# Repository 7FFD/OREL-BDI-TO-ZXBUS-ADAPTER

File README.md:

# OREL-BDI-TO-ZXBUS-ADAPTER

The motivation to create such kind of adapter was a problem to find ready-to-solder boards for ZX Spectrum BDI.
Most of them were designed for specific clones and on Ukrainian marketplaces easily accessible was only boards for Orel BK.

A bit of history...

Somewhere in 2021 I soldered Harlequin 128k and as far as I played with Tape input, decided to expand and connect disk drive.
As I mentioned before, I faced mostly with BDI for Orel computer. Research had shown that all signals on the board were available on Harlequin ZXBUS Edge slot. So, I decided to give a chance and buy this adapter from one of sellers who stated that controller was tested and worked fine. Indeed, he sold DIY package with all components, so, itt was a huge plus.
After I received and soldered it, another kind of issue appeared - how to connect to Harlequin. Solder by wires ZXBUS Slot? Or something else?
I decided to go with adapter, on prototype board solder socket to connect controller and solder ZXBUS Slot with appropriate wiring.
This idea looked more reliable then just wires.

and...

Later I expanded this adapter with optional Kempston Joystick interface, separate TRDOS rom that can in different modes and simple protection schematics for IC KP1818VG93.

The latest version looked like Frankenstien...

Over a time I collected on prototype board quite a lot of useful features and implemented them on final schematic:
 -  Optional Kempston Joystic, can be off, always on or depends on BETA signal from Orel BDI
 -  Optional ROM, can be off, only TRDOS part activated and stock ROM with Basic, TRDOS and Basic in optional ROM, in addition, 27C512 can be used without schematic changes
 -  Magic Button
 -  External +12v
 -  Safe +12V for 1818VG93
 -  Block external Kempston Joystic by /KJOY connected to A28 on ZXBUS Slot

So, I decided make it more beatuful. This is how it looks now!

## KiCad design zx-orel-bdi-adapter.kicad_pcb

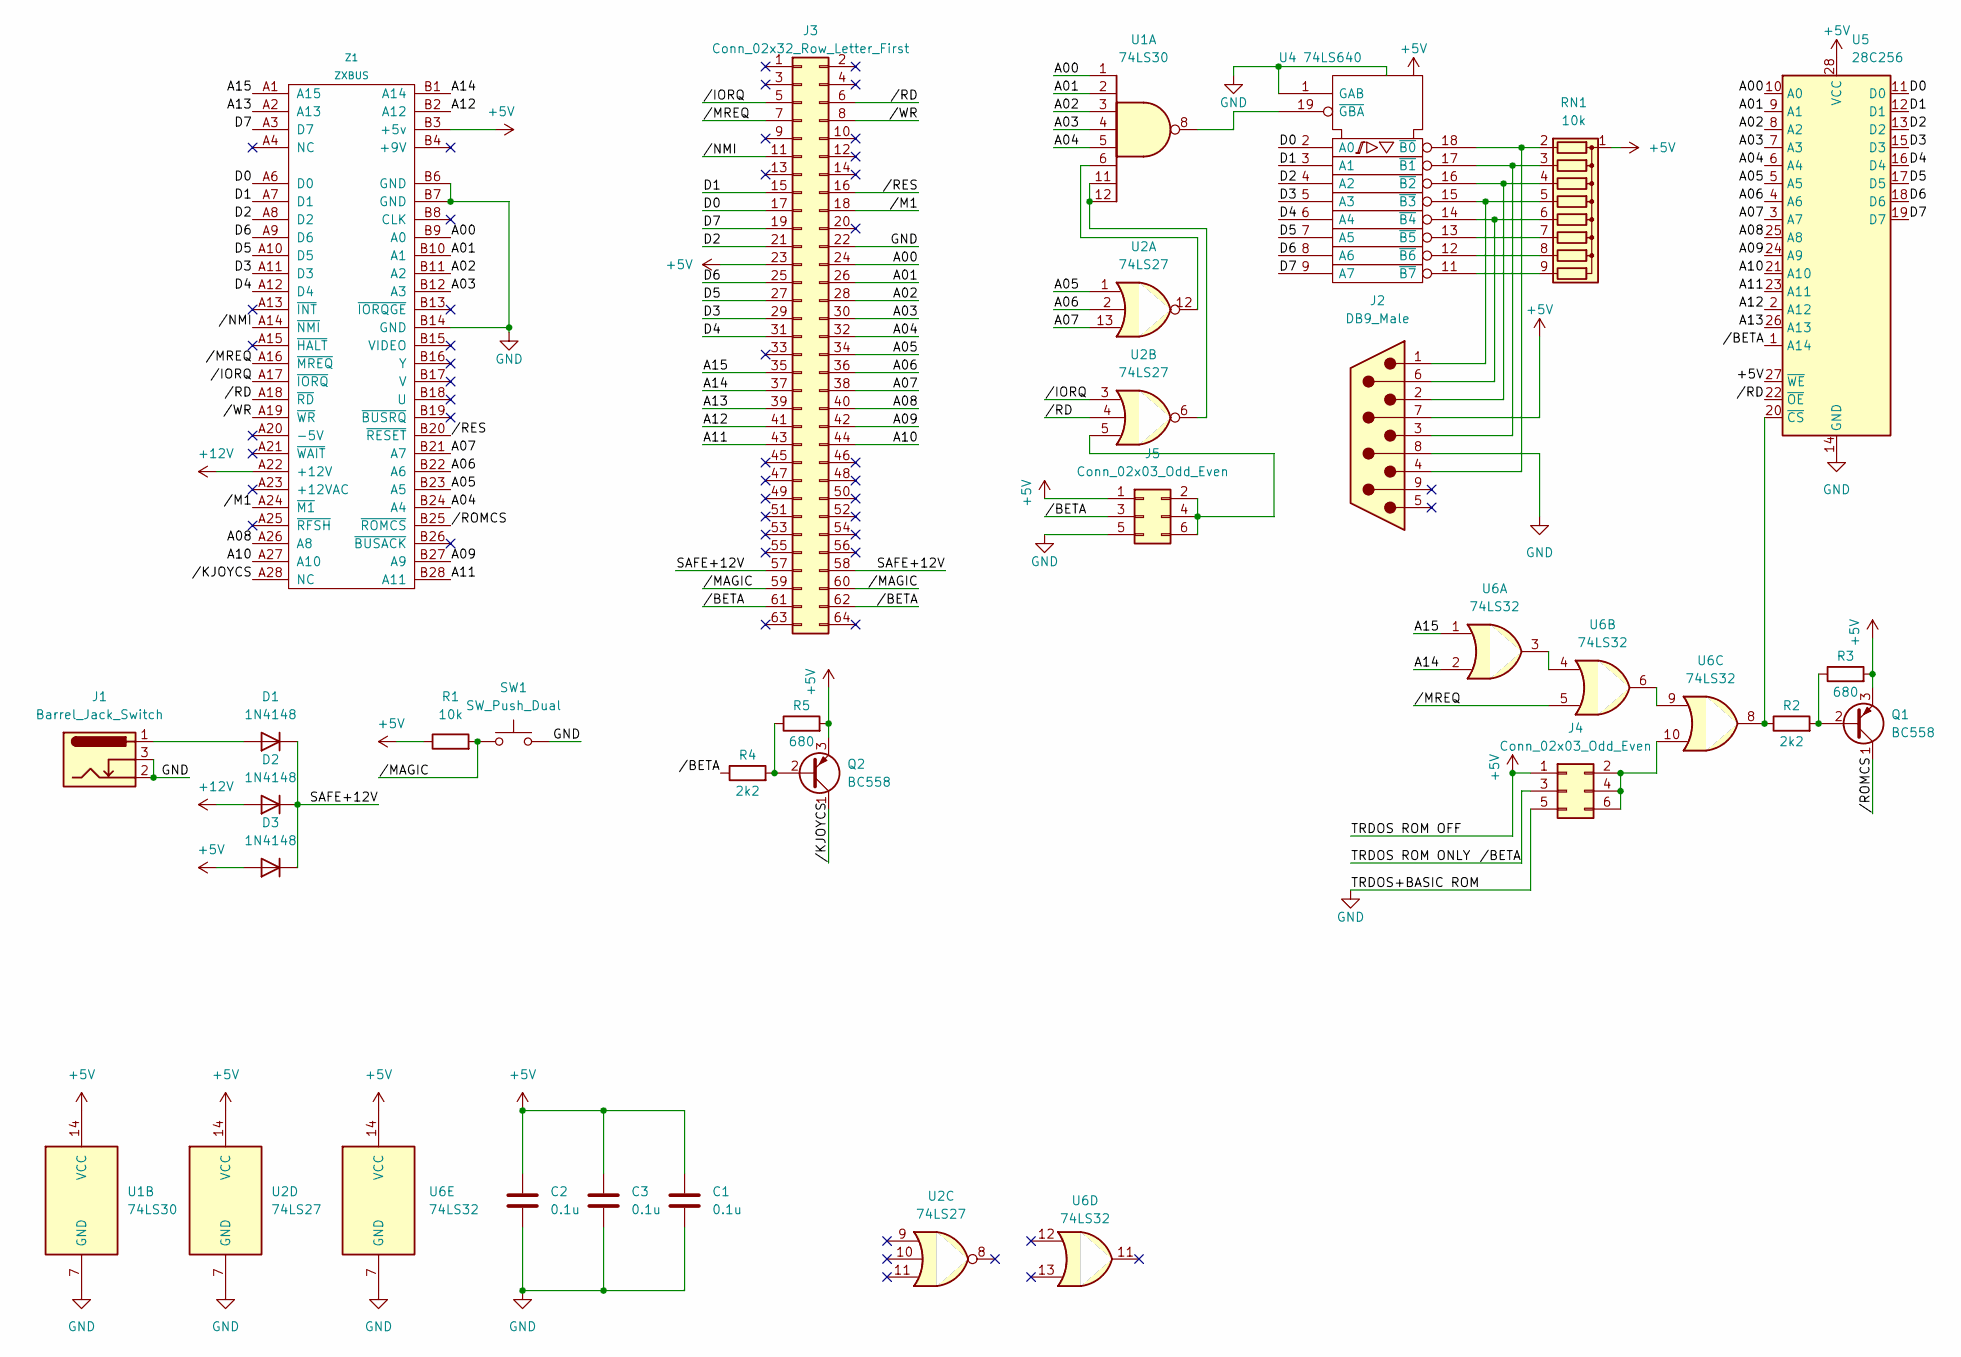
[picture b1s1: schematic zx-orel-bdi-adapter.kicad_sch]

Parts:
C1, C2, C3: 0.1u; C_Disc_D3.8mm_W2.6mm_P2.50mm
D1, D2, D3: 1N4148; D_DO-35_SOD27_P7.62mm_Horizontal
J1: Barrel_Jack_Switch; BarrelJack_Horizontal
J2: DB9_Male; DSUB-9_Male_Horizontal_P2.77x2.84mm_EdgePinOffset4.94mm_Hou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
J3: Conn_02x32_Row_Letter_First; PinHeader_2x32_P2.54mm_Vertical
J4, J5: Conn_02x03_Odd_Even; PinHeader_2x03_P2.54mm_Vertical
Q1, Q2: BC558; TO-92_Inline_Wide
R1: 10k; R_Axial_DIN0207_L6.3mm_D2.5mm_P7.62mm_Horizontal
R2, R4: 2k2; R_Axial_DIN0207_L6.3mm_D2.5mm_P7.62mm_Horizontal
R3, R5: 680; R_Axial_DIN0207_L6.3mm_D2.5mm_P7.62mm_Horizontal
RN1: 10k; R_Array_SIP9
SW1: SW_Push_Dual; SW_TH_Tactile_Omron_B3F-10xx
U1: 74LS30; DIP-14_W7.62mm
U2: 74LS27; DIP-14_W7.62mm
U4: 74LS640; DIP-20_W7.62mm
U5: 28C256; DIP-28_W15.24mm
U6: 74LS32; DIP-14_W7.62mm
Z1: ZXBUS; ZXBUS Slot Connector

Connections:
+5V: C1.1, C2.1, C3.1, D3.2 (A), J2.7, J3.23, J4.1, J5.1, Q1.3 (E), Q2.3 (E), R1.1, R3.2, R5.2, RN1.1 (common), U1.14 (VCC), U2.14 (VCC), U4.20 (VCC), U5.27 (~WE), U5.28 (VCC), U6.14 (VCC), Z1.B3 (+5v)
+12V: D2.2 (A), Z1.A22 (+12V)
/A00: J3.24, U1.1, U5.10 (A0), Z1.B9 (A0)
/A01: J3.26, U1.2, U5.9 (A1), Z1.B10 (A1)
/A02: J3.28, U1.3, U5.8 (A2), Z1.B11 (A2)
/A03: J3.30, U1.4, U5.7 (A3), Z1.B12 (A3)
/A04: J3.32, U1.5, U5.6 (A4), Z1.B24 (A4)
/A05: J3.34, U2.1, U5.5 (A5), Z1.B23 (A5)
/A06: J3.36, U2.2, U5.4 (A6), Z1.B22 (A6)
/A07: J3.38, U2.13, U5.3 (A7), Z1.B21 (A7)
/A08: J3.40, U5.25 (A8), Z1.A26 (A8)
/A09: J3.42, U5.24 (A9), Z1.B27 (A9)
/A10: J3.44, U5.21 (A10), Z1.A27 (A10)
/A11: J3.43, U5.23 (A11), Z1.B28 (A11)
/A12: J3.41, U5.2 (A12), Z1.B2 (A12)
/A13: J3.39, U5.26 (A13), Z1.A2 (A13)
/A14: J3.37, U6.2, Z1.B1 (A14)
/A15: J3.35, U6.1, Z1.A1 (A15)
/D0: J3.17, U4.2 (A0), U5.11 (D0), Z1.A6 (D0)
/D1: J3.15, U4.3 (A1), U5.12 (D1), Z1.A7 (D1)
/D2: J3.21, U4.4 (A2), U5.13 (D2), Z1.A8 (D2)
/D3: J3.29, U4.5 (A3), U5.15 (D3), Z1.A11 (D3)
/D4: J3.31, U4.6 (A4), U5.16 (D4), Z1.A12 (D4)
/D5: J3.27, U4.7 (A5), U5.17 (D5), Z1.A10 (D5)
/D6: J3.25, U4.8 (A6), U5.18 (D6), Z1.A9 (D6)
/D7: J3.19, U4.9 (A7), U5.19 (D7), Z1.A3 (D7)
/SAFE+12V: D1.1 (K), D2.1 (K), D3.1 (K), J3.57, J3.58
/TRDOS ROM ONLY: J3.61, J3.62, J4.3, J5.3, R4.1, U5.1 (A14)
//IORQ: J3.5, U2.3, Z1.A17 (~IORQ)
//KJOYCS: Q2.1 (C), Z1.A28 (NC)
//M1: J3.18, Z1.A24 (~M1)
//MAGIC: J3.59, J3.60, R1.2, SW1.1
//MREQ: J3.7, U6.5, Z1.A16 (~MREQ)
//NMI: J3.11, Z1.A14 (~NMI)
//RD: J3.6, U2.4, U5.22 (~OE), Z1.A18 (~RD)
//RES: J3.16, Z1.B20 (~RESET)
//ROMCS: Q1.1 (C), Z1.B25 (~ROMCS)
//WR: J3.8, Z1.A19 (~WR)
GND: C1.2, C2.2, C3.2, J1.2, J1.3, J2.8, J3.22, J4.5, J5.5, SW1.2, U1.7 (GND), U2.7 (GND), U4.1 (GAB), U4.10 (GND), U5.14 (GND), U6.7 (GND), Z1.B6 (GND), Z1.B7 (GND), Z1.B14 (GND)
unnamed: D1.2 (A), J1.1
unnamed: J4.2, J4.4, J4.6, U6.10
unnamed: J5.2, J5.4, J5.6, U2.5
unnamed: Q1.2 (B), R2.2, R3.1
unnamed: Q2.2 (B), R4.2, R5.1
unnamed: J2.4, RN1.2 (R1), U4.18 (~B0)
unnamed: J2.3, RN1.3 (R2), U4.17 (~B1)
unnamed: J2.2, RN1.4 (R3), U4.16 (~B2)
unnamed: J2.1, RN1.5 (R4), U4.15 (~B3)
unnamed: J2.6, RN1.6 (R5), U4.14 (~B4)
unnamed: RN1.7 (R6), U4.13 (~B5)
unnamed: RN1.8 (R7), U4.12 (~B6)
unnamed: RN1.9 (R8), U4.11 (~B7)
unnamed: U1.6, U2.12
unnamed: U1.11, U1.12, U2.6
unnamed: U1.8, U4.19 (~GBA)
unnamed: R2.1, U5.20 (~CS), U6.8
unnamed: U6.3, U6.4
unnamed: U6.6, U6.9

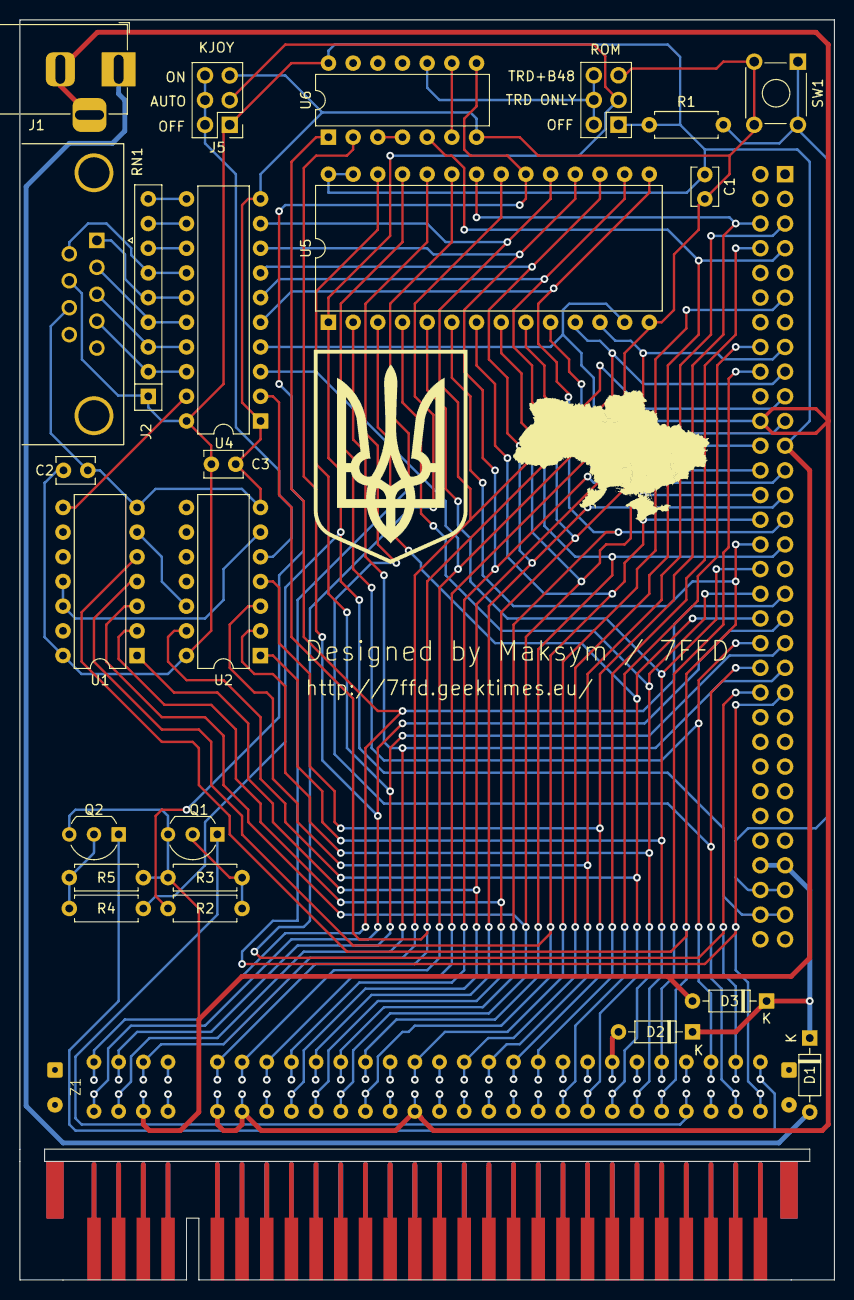
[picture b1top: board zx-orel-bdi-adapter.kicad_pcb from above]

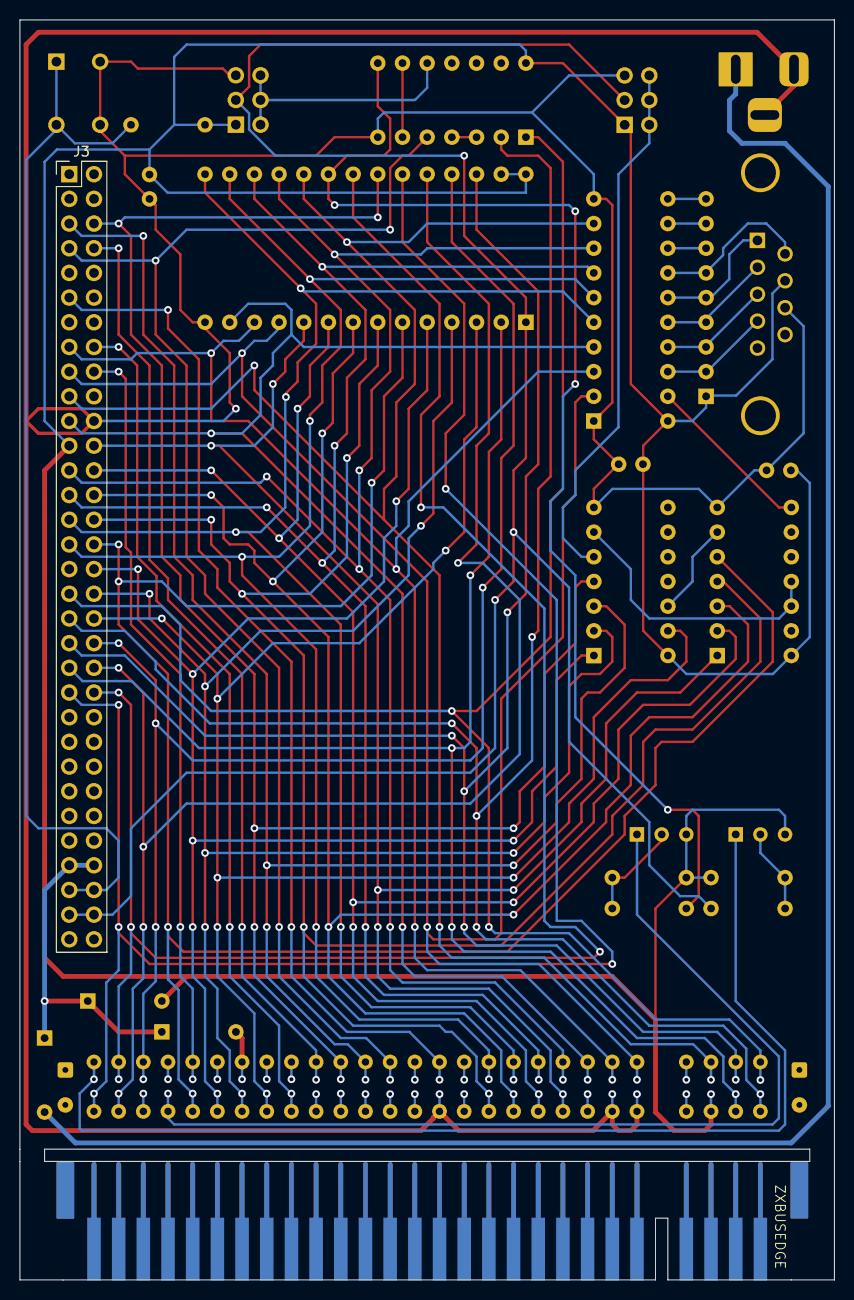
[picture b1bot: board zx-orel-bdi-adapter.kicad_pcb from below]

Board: 2 copper layers, 83.8 x 129.7 mm, 29 parts (2 on the bottom side), 58 nets.

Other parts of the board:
MAP: UA CoA 16x22mm; UA CoA 16x22mm Silk
MAP#2: UA CoA 21x14mm; UA map 21x14mm Silk
ZXBUSEDGE: ZXBUS Edge Connector

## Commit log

2024-10-28 fixed ROMCS activation schematic
2024-10-28 fixed romcs part
2024-10-28 remove from index
2024-10-28 started orel bdi adapter
2024-10-28 changed bc558 schematic
2024-10-28 added BDI schematics
2024-10-28 remove backup
2024-10-28 remove backups
2024-10-28 fixed BETA and /BETA output usage to block TRDOS only and re-routed pcb
2024-10-28 finished orel bdi to zxbus design
2024-10-28 connected kjoycs on schematic
2024-10-28 Fixed bug with flipped TRDOS signal
2024-10-28 added OrelBDI documentation, schematic, dumps, roms and support materials
